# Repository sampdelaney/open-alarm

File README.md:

# open-alarm
Open source domestic alarm system

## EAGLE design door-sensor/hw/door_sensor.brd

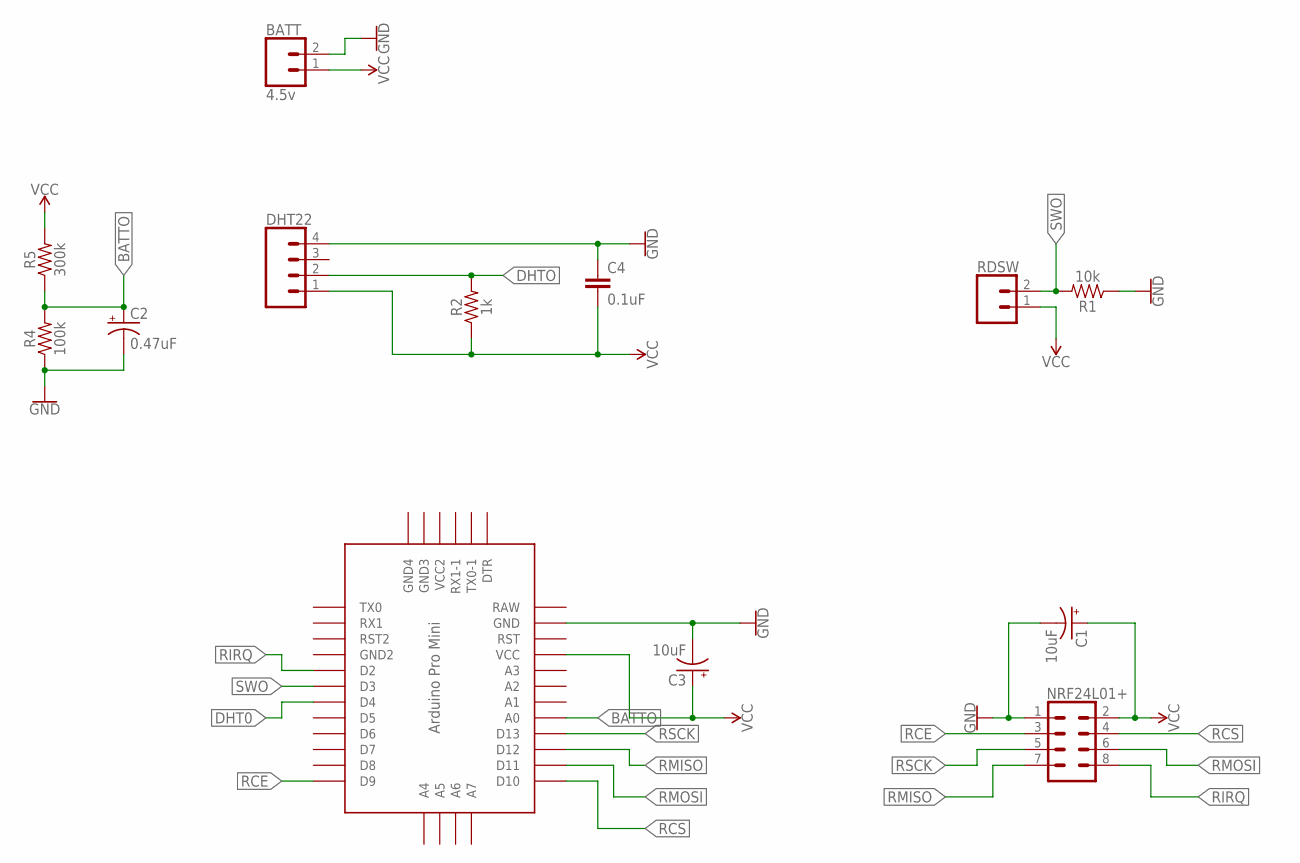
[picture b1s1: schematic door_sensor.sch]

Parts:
BATT: 4.5v; 1X02
C1, C3: 10uF; CPOL-RADIAL-2.5MM-5MM
C2: 0.47uF; CPOL-RADIAL-2.5MM-5MM
C4: 0.1uF; CAP-PTH-SMALL-KIT
DHT22: CONN_04; 1X04
IC1: PRO-MINI
NRF24L01+: CONN_04X2; 2X4
R1: 10k; AXIAL-0.3
R2: 1k; AXIAL-0.3
R4: 100k; AXIAL-0.3
R5: 300k; AXIAL-0.3
RDSW: CONN_02; 1X02

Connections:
BATTO: C2.1 (+), IC1.A0, R4.P$2 (2), R5.P$1 (1)
DHT0: IC1.D4
DHTO: DHT22.2, R2.P$2 (2)
GND: BATT.2, C1.2 (-), C2.2 (-), C3.2 (-), C4.1, DHT22.4, IC1.GND, NRF24L01+.1, R1.P$1 (1), R4.P$1 (1)
RAW: IC1.RAW
RCE: IC1.D9, NRF24L01+.3
RCS: IC1.D10, NRF24L01+.4
RIRQ: IC1.D2, NRF24L01+.8
RMISO: IC1.D12, NRF24L01+.7
RMOSI: IC1.D11, NRF24L01+.6
RSCK: IC1.D13, NRF24L01+.5
SWO: IC1.D3, R1.P$2 (2), RDSW.2
VCC: BATT.1, C1.1 (+), C3.1 (+), C4.2, DHT22.1, IC1.VCC, NRF24L01+.2, R2.P$1 (1), R5.P$2 (2), RDSW.1

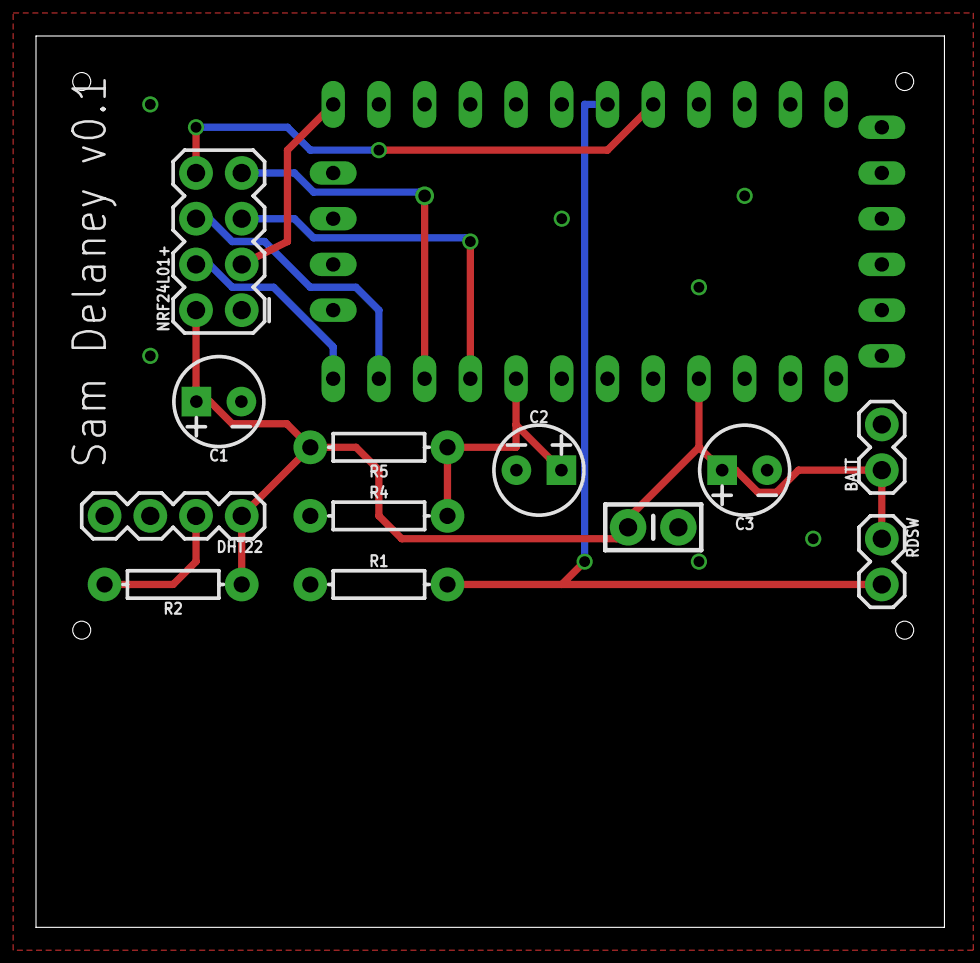
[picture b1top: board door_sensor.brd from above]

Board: 2 copper layers, 50.5 x 49.5 mm, 13 parts (0 on the bottom side), 11 nets.

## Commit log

2017-04-07 initial commit. Included arduino code for remote switch.
2017-04-23 - restructured directories - added eagle files - removed old sw files
2017-05-07 did a load of stuff that I can't remember and hadn't committed for a while
2017-05-07 Added a bunch of libraries that I need to make the door sensor work
2017-05-07 first commit of firmware code (proper)

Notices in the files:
parts and their libraries:
SparkFun-Capacitors: Licensing: Creative Commons ShareAlike 4.0 International - https://creativecommons.org/licenses/by-sa/4.0
